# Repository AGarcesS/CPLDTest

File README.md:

# CPLDTest
Este proyecto consiste en el desarrollo de un sistema de test automatizado para una placa basada en CPLD.
- El directorio *test* cuenta con el software para su ejecución.
- El directorio *rotate_vhdl* incluye el proyecto del diseño VHDL empleado para el test.
- El directorio *esquemas_planos* consta de los esquemas y planos asociados a las placas de circuito impreso y la maqueta desarrolladas.

## Uso
```bash
./test.sh -h

Test funcional para placa basada en CPLD

Sintaxis: test [-h] [-r] puertoSerie

Argumentos de posición:
puertoSerie 	Puerto serie de Arduino
  
Argumentos opcionales:
h     		Imprime esta Ayuda
r    		Ejecuta el test

Ejemplo de uso: ./test.sh -r ttyACM0

```

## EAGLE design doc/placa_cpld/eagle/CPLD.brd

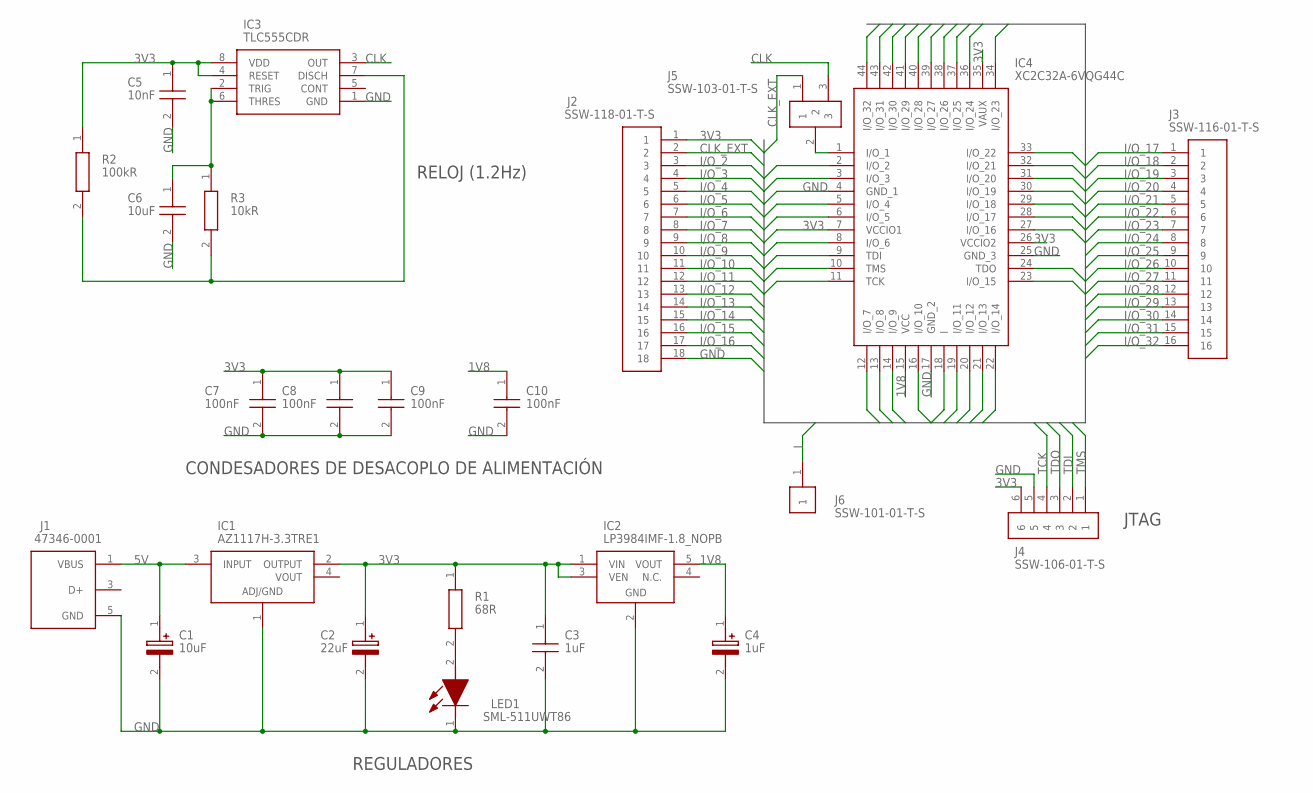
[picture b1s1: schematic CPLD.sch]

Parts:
C1: 10uF; CAPPM3216X180N
C2: 22uF; CAPPM3216X180N
C3: 1uF; CAPC1608X90N
C4: 1uF; CAPPM3216X180N
C5: 10nF; CAPC1608X87N
C6: 10uF; C1608_COMMERCIAL
C7, C8, C9, C10: 100nF; CAPC1608X95N
IC1: AZ1117H-3.3TRE1; SOT230P700X180-4N
IC2: LP3984IMF-1.8_NOPB; SOT95P280X145-5N
IC3: TLC555CDR; SOIC127P600X175-8N
IC4: XC2C32A-6VQG44C; QFP80P1200X1200X120-44N
J1: 47346-0001
J2: SSW-118-01-T-S; SAMTEC_SSW-118-01-T-S
J3: SSW-116-01-T-S; SAMTEC_SSW-116-01-T-S
J4: SSW-106-01-T-S; SAMTEC_SSW-106-01-T-S
J5: SSW-103-01-T-S; SAMTEC_SSW-103-01-T-S
J6: SSW-101-01-T-S; SSW-101-XX-YYY-S
LED1: SML-511UWT86; LEDC1608X65N
R1: 68R; RESC1608X55N
R2: 100kR; RESC1608X55N
R3: 10kR; RESC1608X50N

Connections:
1V8: C4.1 (+), C10.1, IC2.5 (VOUT), IC4.15 (VCC)
3V3: C2.1 (+), C3.1, C5.1, C7.1, C8.1, C9.1, IC1.2 (OUTPUT), IC2.1 (VIN), IC2.3 (VEN), IC3.4 (RESET), IC3.8 (VDD), IC4.7 (VCCIO1), IC4.26 (VCCIO2), IC4.35 (VAUX), J2.1, J4.6, R1.1, R2.1
5V: C1.1 (+), IC1.3 (INPUT), J1.1 (VBUS)
CLK: IC3.3 (OUT), J5.3
CLK_EXT: J2.2, J5.1
GND: C1.2 (-), C2.2 (-), C3.2, C4.2 (-), C5.2, C6.2, C7.2, C8.2, C9.2, C10.2, IC1.1 (ADJ/GND), IC2.2 (GND), IC3.1 (GND), IC4.4 (GND_1), IC4.17 (GND_2), IC4.25 (GND_3), J1.5 (GND), J2.18, J4.5, LED1.1 (K)
I: IC4.18 (I), J6.1
I/O_2: IC4.2 (I/O_2), J2.3
I/O_3: IC4.3 (I/O_3), J2.4
I/O_4: IC4.5 (I/O_4), J2.5
I/O_5: IC4.6 (I/O_5), J2.6
I/O_6: IC4.8 (I/O_6), J2.7
I/O_7: IC4.12 (I/O_7), J2.8
I/O_8: IC4.13 (I/O_8), J2.9
I/O_9: IC4.14 (I/O_9), J2.10
I/O_10: IC4.16 (I/O_10), J2.11
I/O_11: IC4.19 (I/O_11), J2.12
I/O_12: IC4.20 (I/O_12), J2.13
I/O_13: IC4.21 (I/O_13), J2.14
I/O_14: IC4.22 (I/O_14), J2.15
I/O_15: IC4.23 (I/O_15), J2.16
I/O_16: IC4.27 (I/O_16), J2.17
I/O_17: IC4.28 (I/O_17), J3.1
I/O_18: IC4.29 (I/O_18), J3.2
I/O_19: IC4.30 (I/O_19), J3.3
I/O_20: IC4.31 (I/O_20), J3.4
I/O_21: IC4.32 (I/O_21), J3.5
I/O_22: IC4.33 (I/O_22), J3.6
I/O_23: IC4.34 (I/O_23), J3.7
I/O_24: IC4.36 (I/O_24), J3.8
I/O_25: IC4.37 (I/O_25), J3.9
I/O_26: IC4.38 (I/O_26), J3.10
I/O_27: IC4.39 (I/O_27), J3.11
I/O_28: IC4.40 (I/O_28), J3.12
I/O_29: IC4.41 (I/O_29), J3.13
I/O_30: IC4.42 (I/O_30), J3.14
I/O_31: IC4.43 (I/O_31), J3.15
I/O_32: IC4.44 (I/O_32), J3.16
unnamed: C6.1, IC3.2 (TRIG), IC3.6 (THRES), R3.1
unnamed: LED1.2 (A), R1.2
unnamed: IC3.7 (DISCH), R2.2, R3.2
unnamed: IC4.1 (I/O_1), J5.2
TCK: IC4.11 (TCK), J4.4
TDI: IC4.9 (TDI), J4.2
TDO: IC4.24 (TDO), J4.3
TMS: IC4.10 (TMS), J4.1

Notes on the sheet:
JTAG
RELOJ (1.2Hz)
CONDESADORES DE DESACOPLO DE ALIMENTACIÓN
REGULADORES

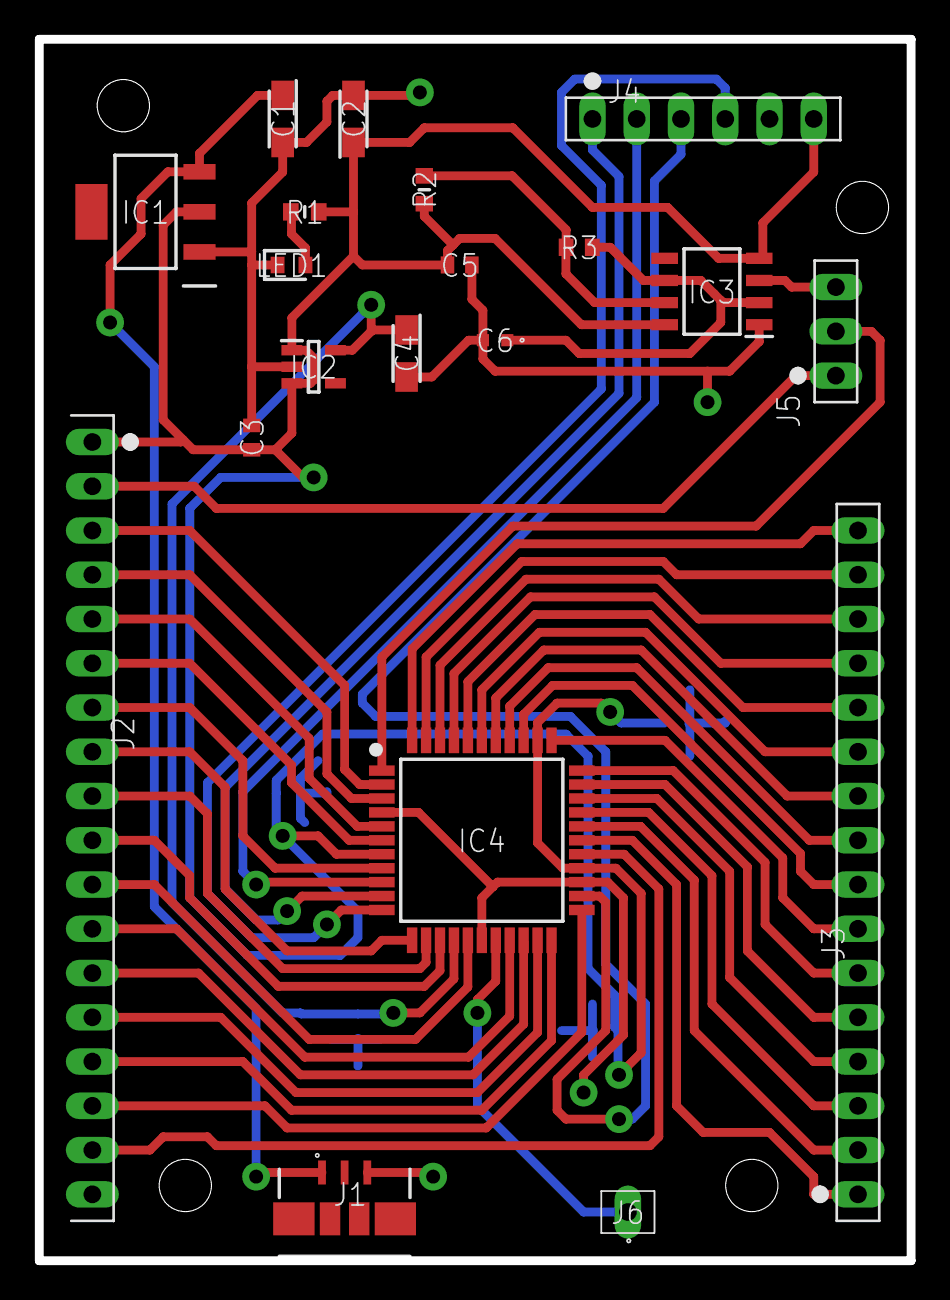
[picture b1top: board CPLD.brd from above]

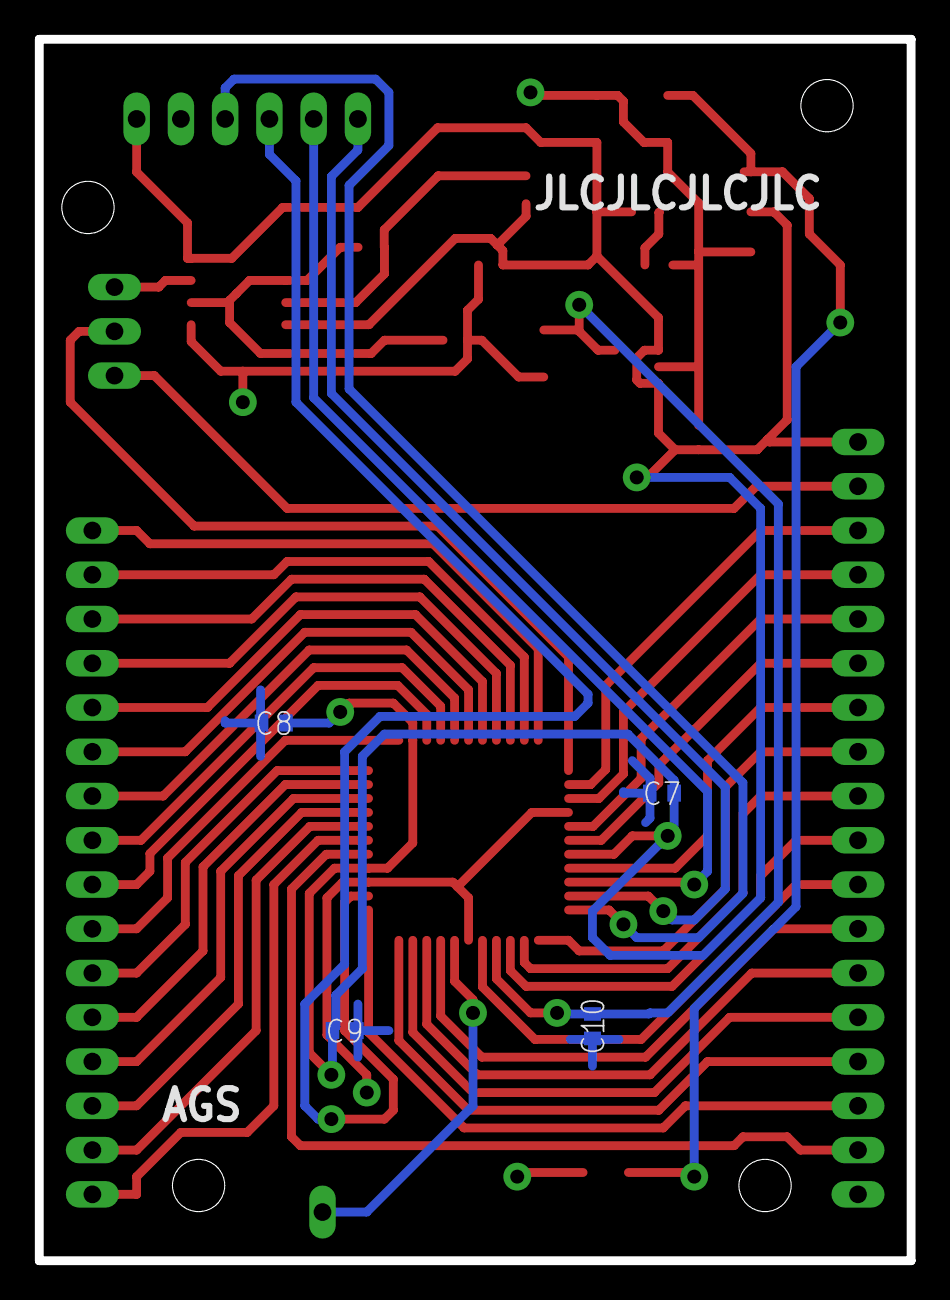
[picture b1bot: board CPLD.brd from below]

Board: 2 copper layers, 50.0 x 70.1 mm, 24 parts (4 on the bottom side), 46 nets.

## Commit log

2022-08-31 Añadido: planos y esquemas de las placas y el soporte
2022-08-31 Añadido: directorio test
2022-08-31 Añadido: proyecto rotate desarrollado en Xilinx ISE
2022-08-31 Añadido: archivo README
2022-09-07 Actualizado: corrección de test.ino y comentarios añadidos en Test.cpp
2022-09-07 Actualizado: corrección de rotate_tb.vhd
2022-09-17 Añadido: manual de instalación, Actualizado: cambio de nombre del directorio de documentación
2025-02-26 Añadido: ficheros de esquemático y rutado del proyecto en Eagle de la placa CPLD
